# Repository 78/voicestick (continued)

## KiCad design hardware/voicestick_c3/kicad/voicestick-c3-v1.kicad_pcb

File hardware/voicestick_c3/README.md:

# VoiceStick C3 v1 hardware design

English · [简体中文](README_ZH.md)

This is the first public hardware version of VoiceStick C3. To order and assemble a device, start with the [build guide](../README.md). The firmware board identifier is `voicestick_c3`.

| Directory or file | Contents |
| --- | --- |
| [kicad/](kicad/) | KiCad project, local symbol and footprint libraries, routed board, ERC and DRC reports |
| [fab/](fab/README.md) | Fabrication guide and PCB renders. Generated manufacturing files use this directory in the build archive. |
| [enclosure/](enclosure/README.md) | FreeCAD scripts, fit checks and assembly instructions. The build archive includes the printable parts and assembly STEP. |
| [tools/](tools/) | Electrical definition, placement, routing, exporters and design checks |
| [assembly-interface.json](assembly-interface.json) | Shared board outline, component positions, clearances and enclosure dimensions |

## Circuit and pins

The QFN32 ESP32-C3 uses a GD25Q64E 8 MB SPI flash, a 40 MHz crystal and a 32.768 kHz sleep crystal. The USB Serial/JTAG console frees the UART0 pins for the keys and LED. A 100 mA TP4054 charger, B5819W USB supply path, AO3401A battery path and RT9080 3.3 V regulator power the board. A second AO3401A switches the microphone and RGB LED together. The SD18OB371-041 bottom-port microphone runs at a default PDM clock of 1.536 MHz, decimated by 96 for 16 kHz audio.

| GPIO | Function |
| --- | --- |
| 0, 1 | 32.768 kHz crystal |
| 2 | Active-low microphone and RGB rail enable, 10 kΩ pull-up |
| 3 | Battery ADC, 1 MΩ / 1 MΩ divider |
| 4 | Main key, active-low wake with 100 kΩ pull-up |
| 5 | USB presence, active-high wake, 100 kΩ / 200 kΩ divider |
| 6, 7 | PDM clock through 33 Ω, and PDM data |
| 8 | Previous key, 10 kΩ boot-strap pull-up |
| 9 | Cancel / BOOT key, 10 kΩ pull-up |
| 10 | TP4054 charging status, active low, enable internal pull-up |
| 11–17 | External flash supply and SPI |
| 18, 19 | USB D− and D+ |
| 20 | WS2812B-2020-V6 data |
| 21 | Next key through 1 kΩ |

The GPIO8 pull-up stays on the previous key to avoid back-powering the unpowered LED. GPIO20 floats before deep sleep. After one hour idle on battery, or one minute without a connected host, the main key or USB can wake the board. The low-battery path uses USB-only wake after three readings below 3.5 V.

## Editing and rebuilding

For full populated PCB and assembly STEP exports, unpack the matching component model archive as described under [v1 release files](../README.md#v1-release-files). Circuit edits, routing and electrical checks can be done from the source checkout alone. For an enclosure-only rebuild, extract `fab/voicestick-c3-v1.step` from the build archive to include the populated PCB.

Edit connectivity and component selections in [design.py](tools/design.py), drawing layout in [schematic_layout.py](tools/schematic_layout.py) and board placement in [placement.py](tools/placement.py). The generated KiCad files are available for inspection and fabrication. The electrical definition also drives the BOM and the pin-by-pin netlist check.

The build script uses the macOS application paths for KiCad 10 and FreeCAD 1.1. Install KiCadRoutingTools with its Python virtual environment under `~/tools/KiCadRoutingTools`, or point `KRT` at the checkout. [KiCadRoutingTools](https://github.com/drandyhaas/KiCadRoutingTools)

```sh
cd hardware/voicestick_c3
./make.sh             # Complete PCB and enclosure build
./make.sh board       # Through board DRC and geometry checks
./make.sh enclosure   # Rebuild enclosure from the existing board
```

The build generates the libraries, schematic, BOM and netlist, places the footprints, locks critical copper, routes the other nets and refills the planes. It checks schematic parity and board rules before exporting the manufacturing files and enclosure models. The fixed UUID seeds and clean intermediate directory keep the routing order reproducible. After layout changes, `python3 tools/seed_search.py --sets 0-29 --jobs 5` compares route quality. The current layout uses seed set 8.

## Layout and components

The board measures 50 × 30 × 1.0 mm with four copper layers, internal GND and +3V3 planes, and components on top. RF, USB, clocks, flash, decoupling and the power trunks have locked routing. Signal and light-load branches use 0.45/0.3 mm vias. Supply trunks and ground stitching use 0.6/0.3 mm vias. U1's nine thermal vias are the only vias in pads. The USB traces are short and the case limits antenna clearance, so RF matching is checked with the case fitted.

The main switch is CPG151101D05, and the three side switches are Alps SKRTLBE010. The build archive’s `fab/voicestick-c3-v1-bom.csv` lists manufacturer and LCSC numbers. The custom 3D library includes aligned EasyEDA models or size substitutes for the side switch, microphone, antenna and LEDs. The main switch model is generated from the mechanical interface. Clearance checks use component envelopes.

## First-board checks

ERC, DRC, netlist parity and enclosure geometry are checked by the build. The nine STL meshes are closed. Record physical results separately:

1. Verify the BOM matches and placement rotations in the order preview. Confirm the RF feed impedance with the selected JLC04101H-3313 stack-up.
2. Print the fit coupon and acoustic test box. Check the stem, screw pilots, key travel and microphone seal.
3. Check the supply rails over USB before connecting a battery. Measure crystal offset, PDM clock, microphone format and noise. Tune chip-side matching first, then measure antenna matching and range with the enclosure fitted.
4. On battery power, measure deep-sleep current at J2. The design estimate is 12–20 µA. Check reverse leakage through D1 and that the charging LED goes out with USB removed. Verify that low-battery shutdown wakes only on USB insertion.

The [fabrication guide](fab/README.md) and [enclosure guide](enclosure/README.md) give the test points and assembly details.

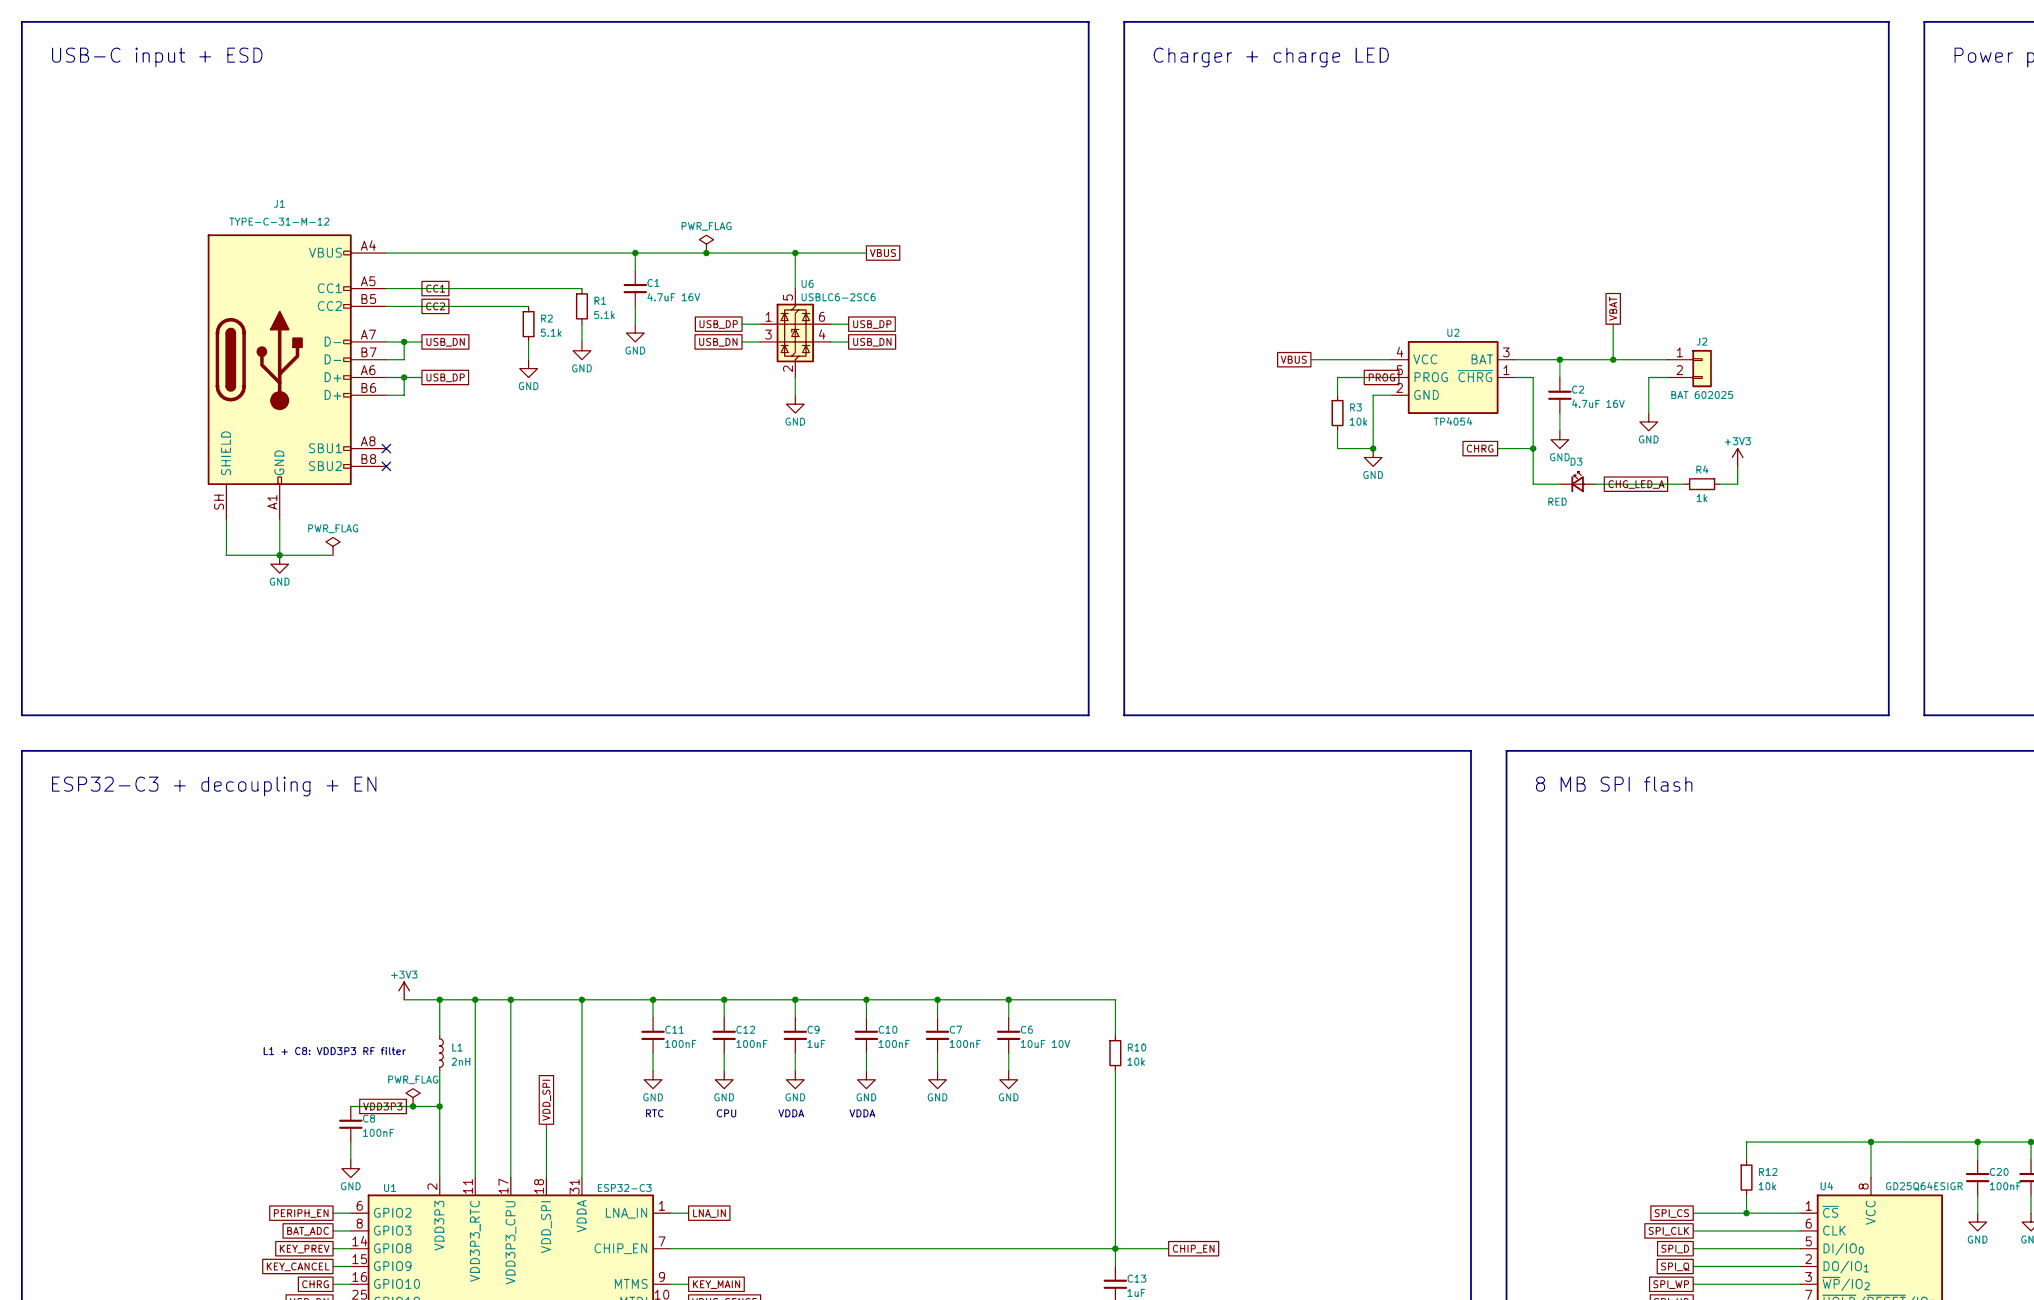
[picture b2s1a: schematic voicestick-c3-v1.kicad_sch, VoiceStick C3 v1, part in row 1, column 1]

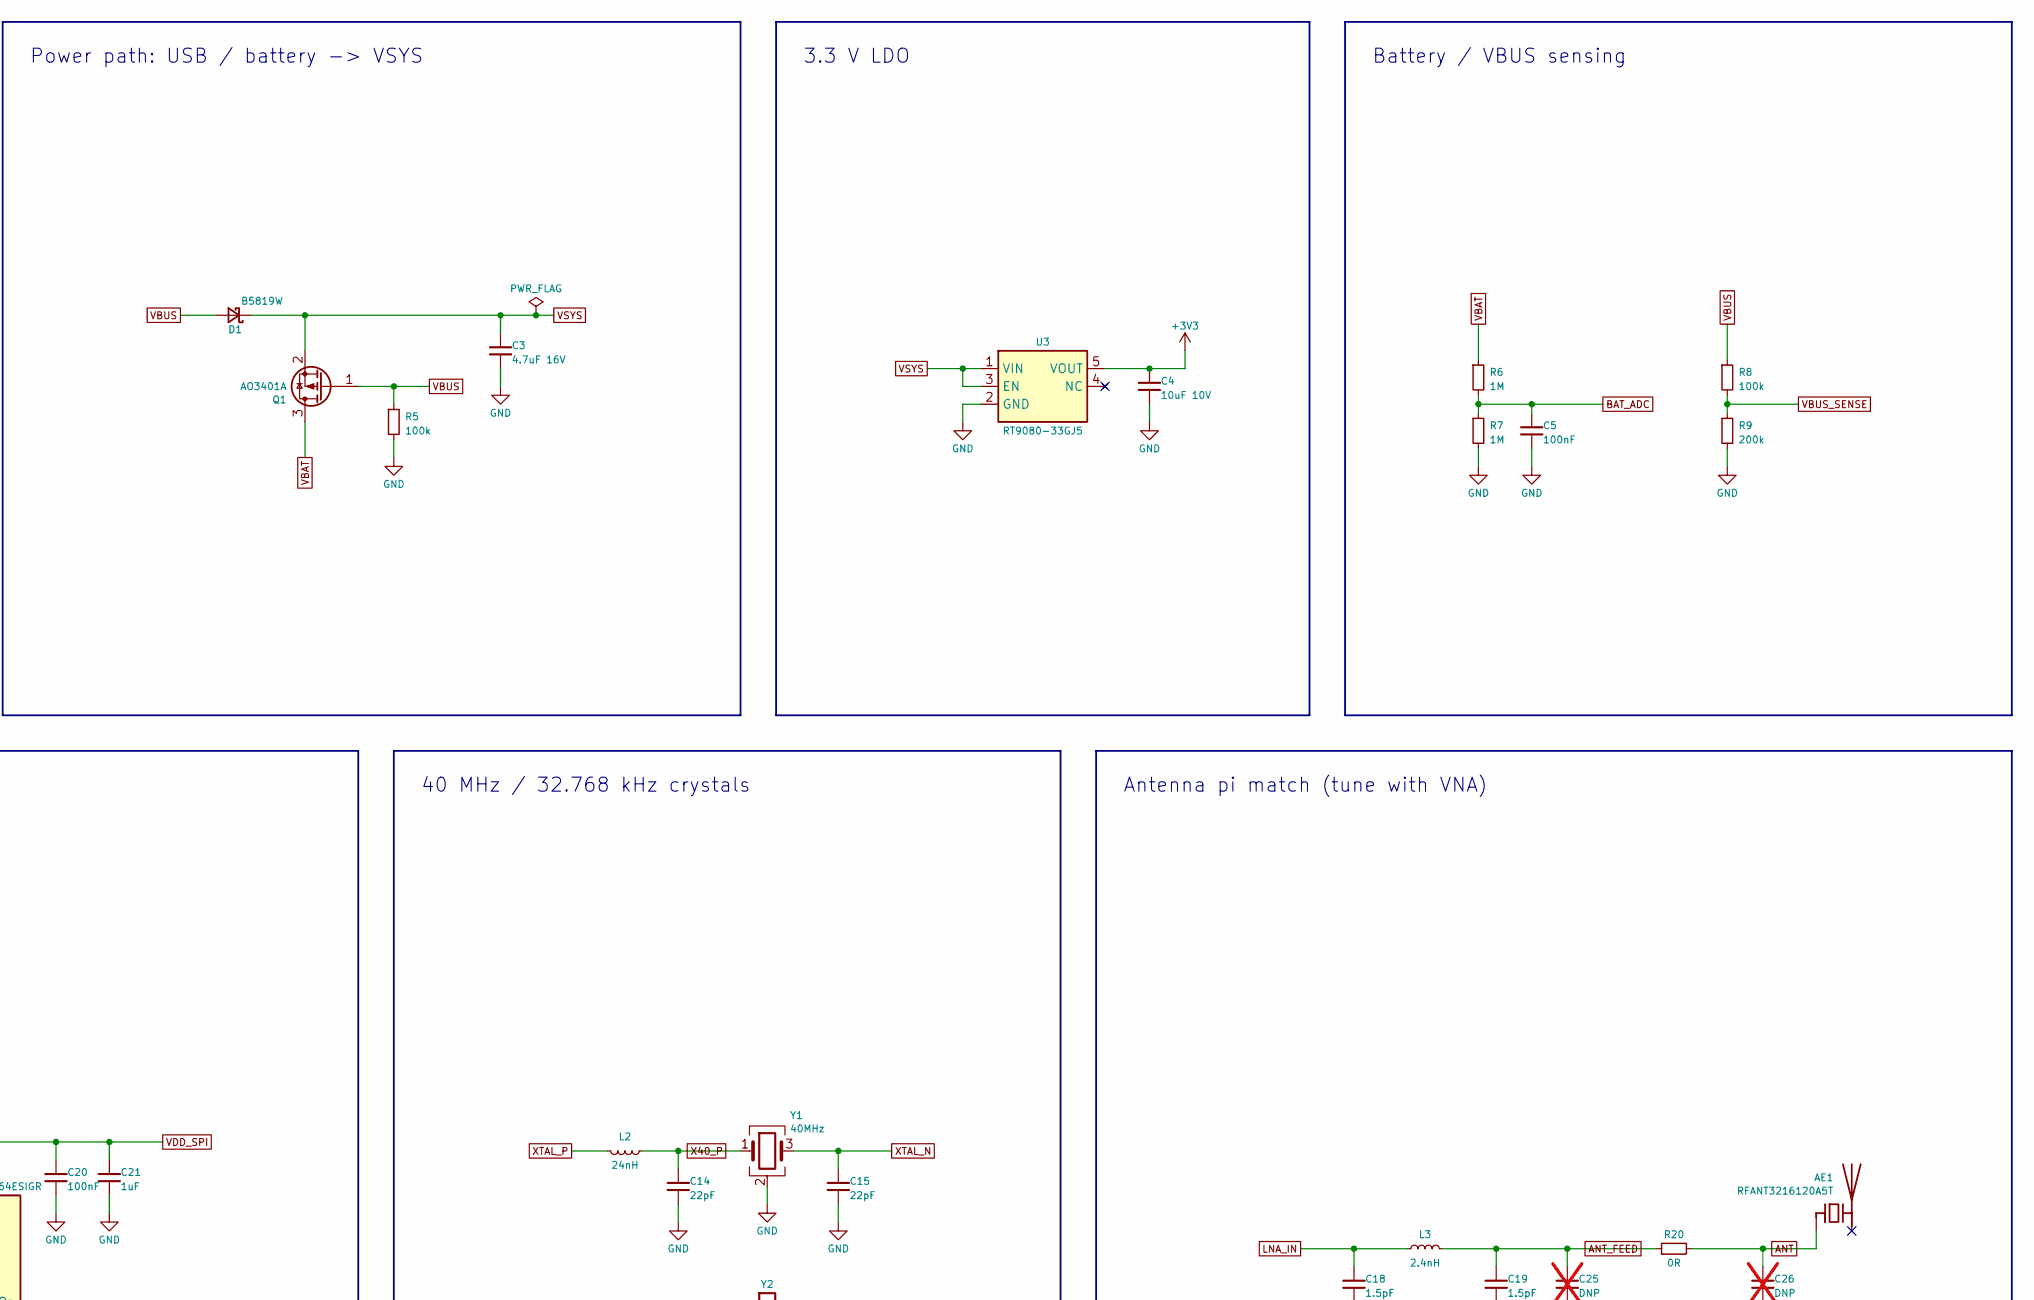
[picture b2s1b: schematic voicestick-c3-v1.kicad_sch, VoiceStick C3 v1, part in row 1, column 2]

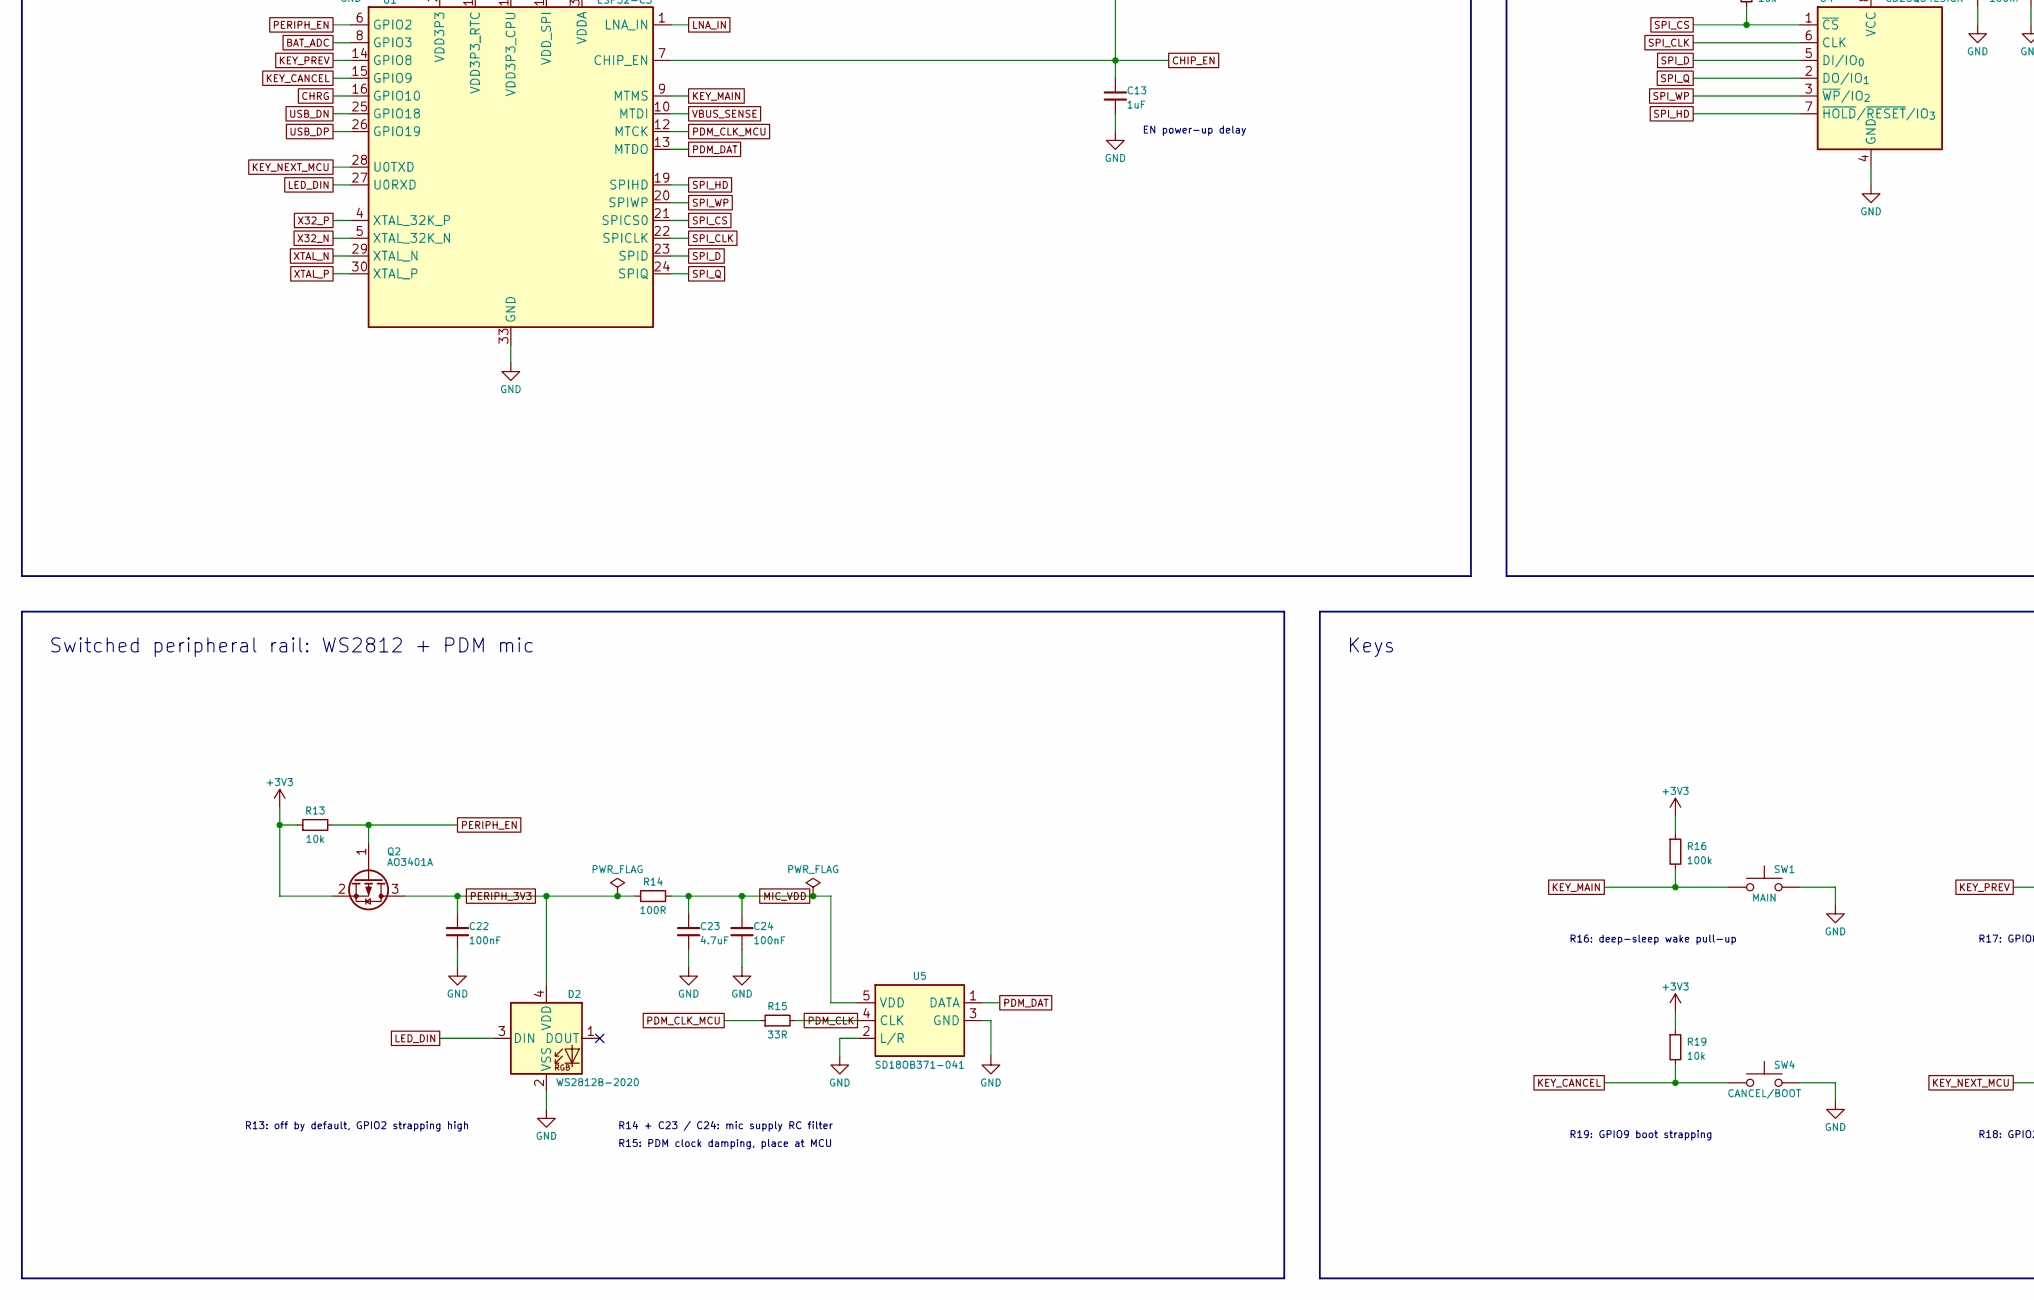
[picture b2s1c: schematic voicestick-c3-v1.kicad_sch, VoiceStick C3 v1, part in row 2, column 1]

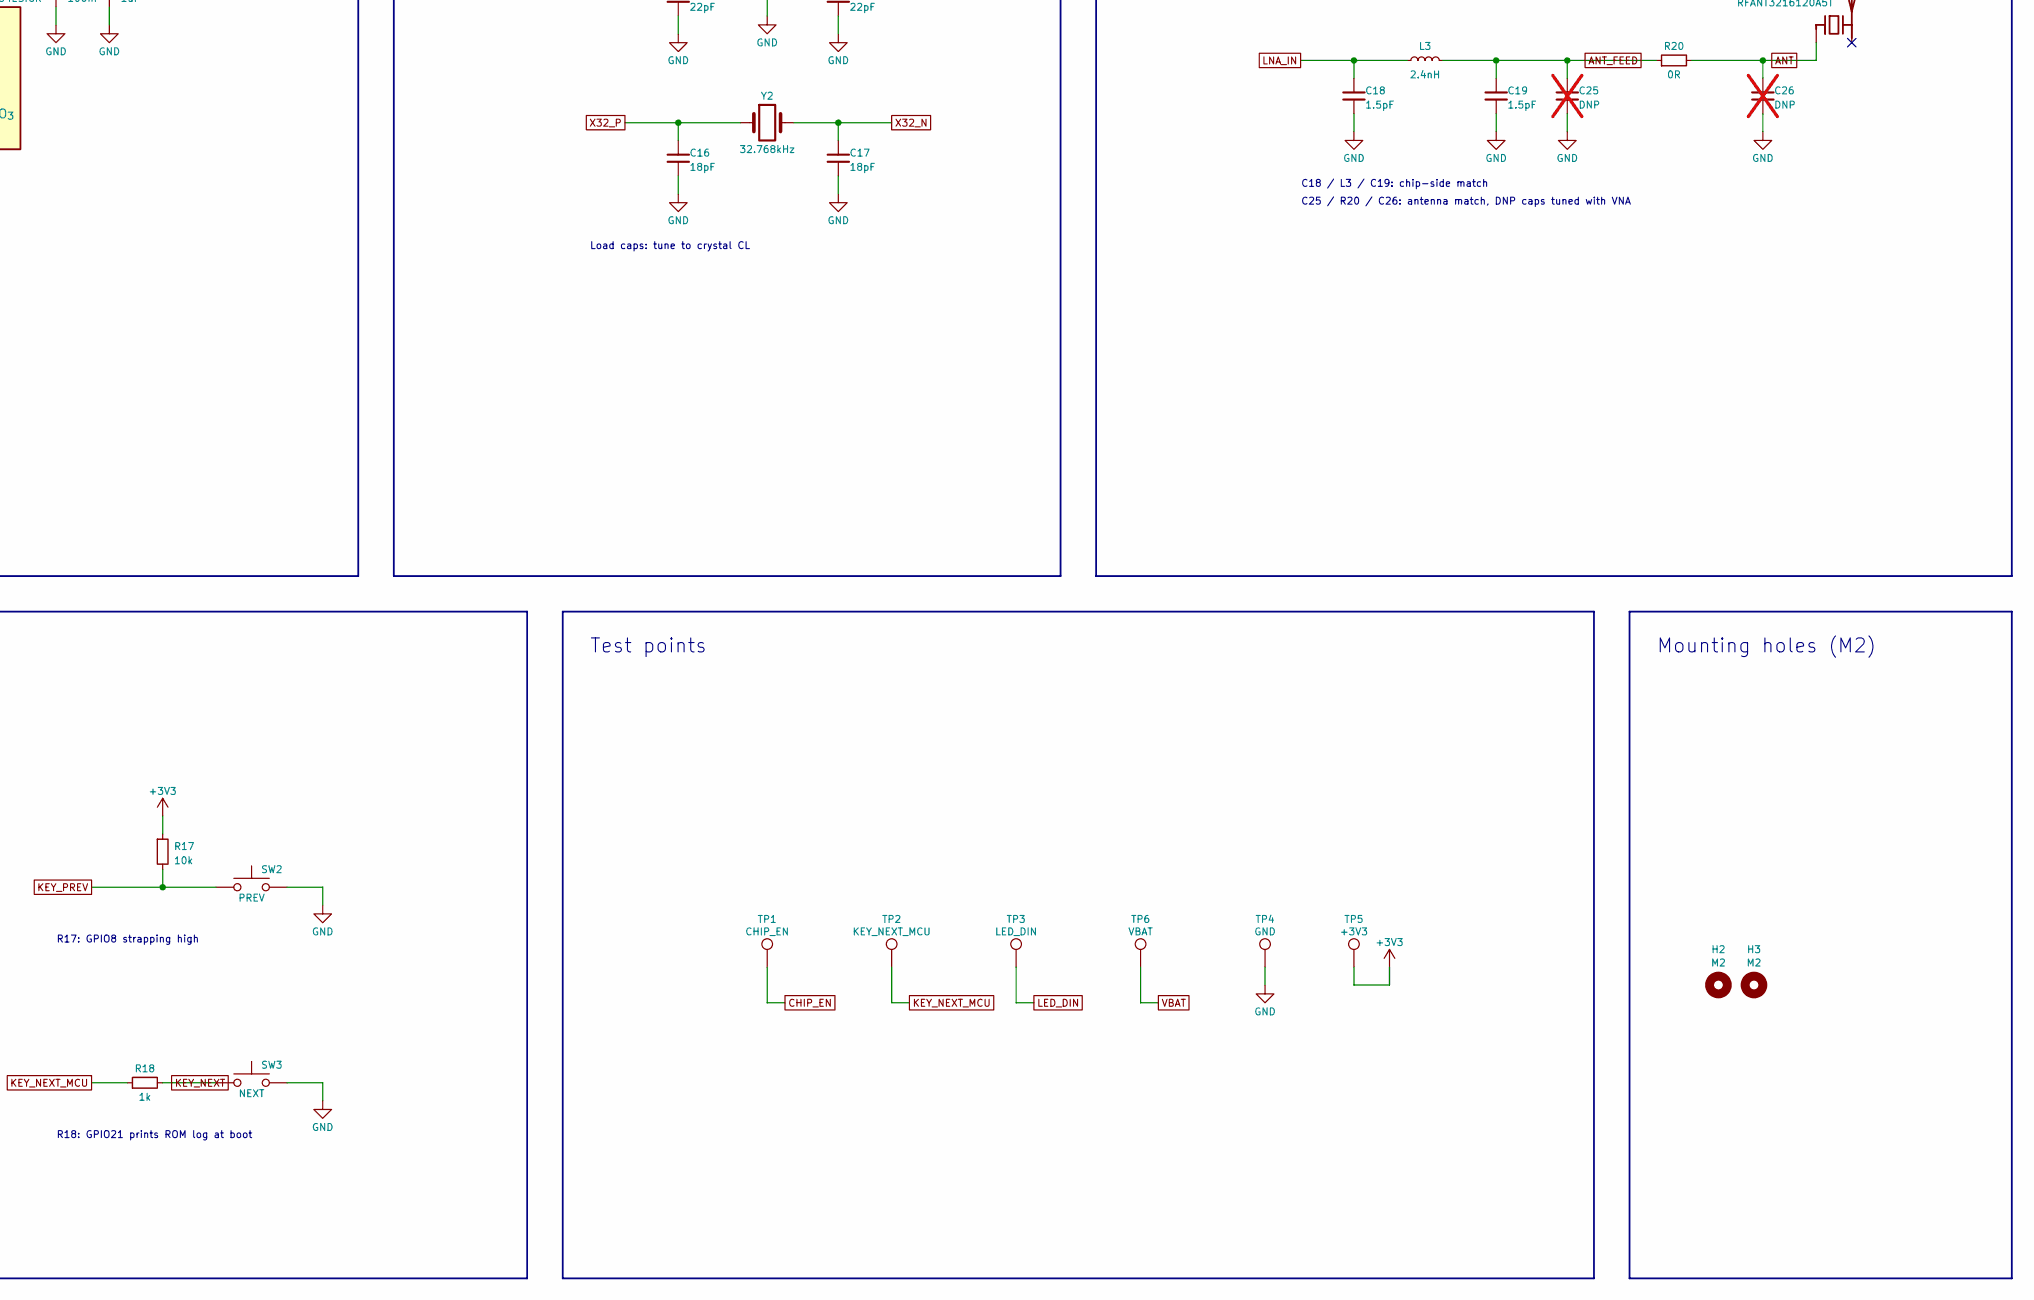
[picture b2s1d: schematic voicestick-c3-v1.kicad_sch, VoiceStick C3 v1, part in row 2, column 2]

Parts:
AE1: RFANT3216120A5T; ChipAntenna_3216; MPN Walsin RFANT3216120A5T; LCSC C127629
C1, C2, C3: 4.7uF 16V; C_0603_1608Metric; MPN CL10A475KO8NNNC; LCSC C19666
C4, C6: 10uF 10V; C_0603_1608Metric; MPN CL10A106KP8NNNC; LCSC C19702
C5, C7, C8, C10, C11, C12, C20, C22, C24: 100nF; C_0402_1005Metric; MPN CL05B104KO5NNNC; LCSC C1525
C9, C13, C21: 1uF; C_0402_1005Metric; MPN CL05A105KA5NQNC; LCSC C52923
C14, C15: 22pF; C_0402_1005Metric; MPN 0402CG220J500NT; LCSC C1555
C16, C17: 18pF; C_0402_1005Metric; MPN 0402CG180J500NT; LCSC C1549
C18, C19: 1.5pF; C_0402_1005Metric; MPN 0402CG1R5C500NT; LCSC C1552
C23: 4.7uF; C_0402_1005Metric; MPN CL05A475MP5NRNC; LCSC C23733
C25, C26: DNP; C_0402_1005Metric; MPN DNP; not fitted
D1: B5819W; D_SOD-123; MPN B5819W SL; LCSC C8598
D2: WS2812B-2020; LED_WS2812B-2020_PLCC4_2.0x2.0mm; MPN Worldsemi WS2812B-2020-V6; LCSC C52917434
D3: RED; LED_LiteOn_LTST-S270; MPN Lite-On LTST-S270KRKT; LCSC C125114
H2, H3: M2; MountingHole_2.2mm_M2; MPN M2
J1: TYPE-C-31-M-12; USB_C_Receptacle_HRO_TYPE-C-31-M-12; MPN HRO TYPE-C-31-M-12; LCSC C165948
J2: BAT 602025; JST_SH_SM02B-SRSS-TB_1x02-1MP_P1.00mm_Horizontal; MPN JST SM02B-SRSS-TB(LF)(SN); LCSC C160402
L1: 2nH; L_0402_1005Metric; MPN Murata LQG15HS2N0S02D; LCSC C18216
L2: 24nH; L_0402_1005Metric; MPN Sunlord SDCL1005C24NJTDF; LCSC C74301
L3: 2.4nH; L_0402_1005Metric; MPN Murata LQG15HS2N4S02D; LCSC C97997
Q1, Q2: AO3401A; SOT-23; MPN AO3401A; LCSC C15127
R1, R2: 5.1k; R_0402_1005Metric; MPN 0402WGF5101TCE; LCSC C25905
R3, R10, R12, R13, R17, R19: 10k; R_0402_1005Metric; MPN 0402WGF1002TCE; LCSC C25744
R4, R18: 1k; R_0402_1005Metric; MPN 0402WGF1001TCE; LCSC C11702
R5, R8, R16: 100k; R_0402_1005Metric; MPN 0402WGF1003TCE; LCSC C25741
R6, R7: 1M; R_0402_1005Metric; MPN 0402WGF1004TCE; LCSC C26083
R9: 200k; R_0402_1005Metric; MPN 0402WGF2003TCE; LCSC C25764
R14: 100R; R_0402_1005Metric; MPN 0402WGF1000TCE; LCSC C25076
R15: 33R; R_0402_1005Metric; MPN 0402WGF330JTCE; LCSC C25105
R20: 0R; R_0402_1005Metric; MPN 0402WGF0000TCE; LCSC C17168
SW1: MAIN; CPG151101D05; MPN Kailh CPG151101D05; LCSC C49234236
SW2: PREV; Alps_SKRTLBE010; MPN Alps SKRTLBE010; LCSC C127481
SW3: NEXT; Alps_SKRTLBE010; MPN Alps SKRTLBE010; LCSC C127481
SW4: CANCEL/BOOT; Alps_SKRTLBE010; MPN Alps SKRTLBE010; LCSC C127481
TP1: CHIP_EN; TestPoint_Pad_D1.0mm; MPN CHIP_EN
TP2: KEY_NEXT_MCU; TestPoint_Pad_D1.0mm; MPN KEY_NEXT_MCU
TP3: LED_DIN; TestPoint_Pad_D1.0mm; MPN LED_DIN
TP4: GND; TestPoint_Pad_D1.0mm; MPN GND
TP5: +3V3; TestPoint_Pad_D1.0mm; MPN +3V3
TP6: VBAT; TestPoint_Pad_D1.0mm; MPN VBAT
U1: ESP32-C3; QFN-32-1EP_5x5mm_P0.5mm_EP3.7x3.7mm; MPN ESP32-C3 (QFN32, no flash); LCSC C2838500
U2: TP4054; SOT-23-5; MPN TOP POWER TP4054-42-SOT25R; LCSC C32574
U3: RT9080-33GJ5; SOT-23-5; MPN Richtek RT9080-33GJ5 (TSOT-23-5); LCSC C841192
U4: GD25Q64ESIGR; SOIC-8_5.3x5.3mm_P1.27mm; MPN GigaDevice GD25Q64ESIGR (8 MB, 208 mil); LCSC C2831359
U5: SD18OB371-041; Goertek_SD18OB371-041; MPN SD18OB371-041; LCSC C3040249
U6: USBLC6-2SC6; SOT-23-6; MPN USBLC6-2SC6; LCSC C7519
Y1: 40MHz; Crystal_SMD_3225-4Pin_3.2x2.5mm; MPN Yangxing X322540MPB4SI (CL=15pF +-10ppm); LCSC C9010
Y2: 32.768kHz; Crystal_SMD_3215-2Pin_3.2x1.5mm; MPN 32.768 kHz 3215 CL=12.5pF; LCSC C32346

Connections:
+3V3: C4.1, C6.1, C7.1, C9.1, C10.1, C11.1, C12.1, L1.1, Q2.2 (S), R4.1, R10.1, R13.1, R16.1, R17.1, R19.1, TP5.1, U1.11 (VDD3P3_RTC), U1.17 (VDD3P3_CPU), U1.31 (VDDA), U1.32 (VDDA), U3.5 (VOUT)
ANT: AE1.1 (FEED), C26.1, R20.2
ANT_FEED: C19.1, C25.1, L3.2, R20.1
BAT_ADC: C5.1, R6.2, R7.1, U1.8 (GPIO3)
CC1: J1.A5 (CC1), R1.1
CC2: J1.B5 (CC2), R2.1
CHG_LED_A: D3.2 (A), R4.2
CHIP_EN: C13.1, R10.2, TP1.1, U1.7 (CHIP_EN)
CHRG: D3.1 (K), U1.16 (GPIO10), U2.1 (~CHRG)
GND: C1.2, C2.2, C3.2, C4.2, C5.2, C6.2, C7.2, C8.2, C9.2, C10.2, C11.2, C12.2, C13.2, C14.2, C15.2, C16.2, C17.2, C18.2, C19.2, C20.2, C21.2, C22.2, C23.2, C24.2, C25.2, C26.2, D2.2 (VSS), J1.A1 (GND), J1.A12 (GND), J1.B1 (GND), J1.B12 (GND), J1.SH (SHIELD), J2.2, R1.2, R2.2, R3.2, R5.2, R7.2, R9.2, SW1.2, SW2.2, SW3.2, SW4.2, TP4.1, U1.33 (GND), U2.2 (GND), U3.2 (GND), U4.4 (GND), U5.2 (L/R), U5.3 (GND), U6.2 (GND), Y1.2 (G), Y1.4 (G)
KEY_CANCEL: R19.2, SW4.1, U1.15 (GPIO9)
KEY_MAIN: R16.2, SW1.1, U1.9 (MTMS)
KEY_NEXT: R18.2, SW3.1
KEY_NEXT_MCU: R18.1, TP2.1, U1.28 (U0TXD)
KEY_PREV: R17.2, SW2.1, U1.14 (GPIO8)
LED_DIN: D2.3 (DIN), TP3.1, U1.27 (U0RXD)
LNA_IN: C18.1, L3.1, U1.1 (LNA_IN)
MIC_VDD: C23.1, C24.1, R14.2, U5.5 (VDD)
PDM_CLK: R15.2, U5.4 (CLK)
PDM_CLK_MCU: R15.1, U1.12 (MTCK)
PDM_DAT: U1.13 (MTDO), U5.1 (DATA)
PERIPH_3V3: C22.1, D2.4 (VDD), Q2.3 (D), R14.1
PERIPH_EN: Q2.1 (G), R13.2, U1.6 (GPIO2)
PROG: R3.1, U2.5 (PROG)
SPI_CLK: U1.22 (SPICLK), U4.6 (CLK)
SPI_CS: R12.2, U1.21 (SPICS0), U4.1 (~CS)
SPI_D: U1.23 (SPID), U4.5 (DI/IO_{0})
SPI_HD: U1.19 (SPIHD), U4.7 (~HOLD/~RESET/IO_{3})
SPI_Q: U1.24 (SPIQ), U4.2 (DO/IO_{1})
SPI_WP: U1.20 (SPIWP), U4.3 (~WP/IO_{2})
USB_DN: J1.A7 (D-), J1.B7 (D-), U1.25 (GPIO18), U6.3 (I/O2), U6.4 (I/O2)
USB_DP: J1.A6 (D+), J1.B6 (D+), U1.26 (GPIO19), U6.1 (I/O1), U6.6 (I/O1)
VBAT: C2.1, J2.1, Q1.3 (D), R6.1, TP6.1, U2.3 (BAT)
VBUS: C1.1, D1.2 (A), J1.A4 (VBUS), J1.A9 (VBUS), J1.B4 (VBUS), J1.B9 (VBUS), Q1.1 (G), R5.1, R8.1, U2.4 (VCC), U6.5 (VBUS)
VBUS_SENSE: R8.2, R9.1, U1.10 (MTDI)
VDD3P3: C8.1, L1.2, U1.2 (VDD3P3), U1.3 (VDD3P3)
VDD_SPI: C20.1, C21.1, R12.1, U1.18 (VDD_SPI), U4.8 (VCC)
VSYS: C3.1, D1.1 (K), Q1.2 (S), U3.1 (VIN), U3.3 (EN)
X32_N: C17.1, U1.5 (XTAL_32K_N), Y2.2
X32_P: C16.1, U1.4 (XTAL_32K_P), Y2.1
X40_P: C14.1, L2.1, Y1.1
XTAL_N: C15.1, U1.29 (XTAL_N), Y1.3
XTAL_P: L2.2, U1.30 (XTAL_P)

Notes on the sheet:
USB-C input + ESD
Charger + charge LED
Power path: USB / battery -> VSYS
3.3 V LDO
Battery / VBUS sensing
RTC
CPU
VDDA
L1 + C8: VDD3P3 RF filter
EN power-up delay
ESP32-C3 + decoupling + EN
8 MB SPI flash
Load caps: tune to crystal CL
40 MHz / 32.768 kHz crystals
C18 / L3 / C19: chip-side match
C25 / R20 / C26: antenna match, DNP caps tuned with VNA
Antenna pi match (tune with VNA)
R13: off by default, GPIO2 strapping high
R14 + C23 / C24: mic supply RC filter
R15: PDM clock damping, place at MCU
Switched peripheral rail: WS2812 + PDM mic
R16: deep-sleep wake pull-up
R17: GPIO8 strapping high
R19: GPIO9 boot strapping
R18: GPIO21 prints ROM log at boot
Keys
Test points
Mounting holes (M2)

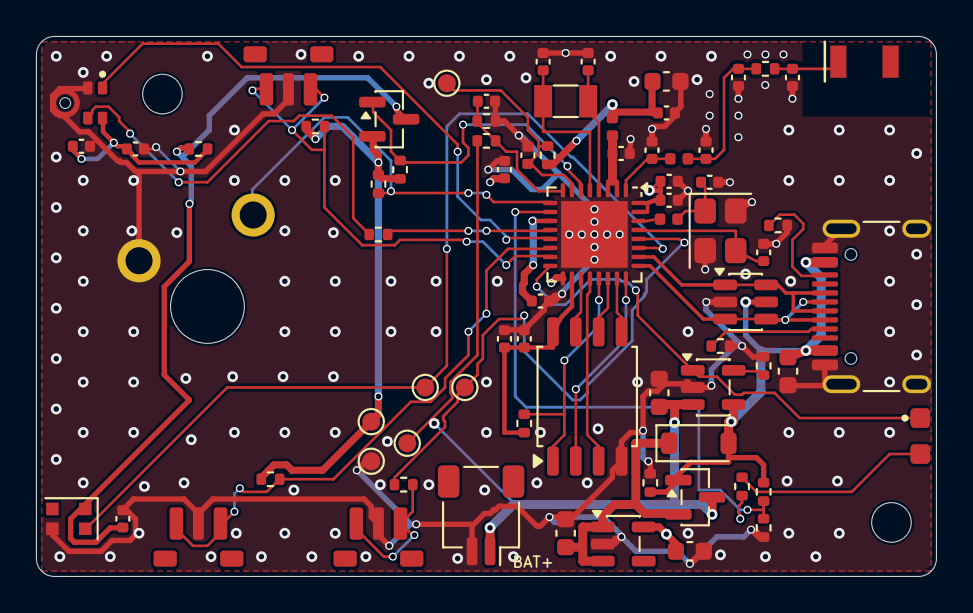
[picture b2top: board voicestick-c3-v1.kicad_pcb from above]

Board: 4 copper layers, 50.0 x 30.0 mm, 76 parts (0 on the bottom side), 43 nets.
